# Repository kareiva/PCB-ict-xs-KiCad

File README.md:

# PCB-ict-xs-KiCad

The ICT tracker KiCad PCB imported from @micked99's Eagle version

Based on original ict_v361-xs, using the QFN/MLF version of the 328p.

Software for this board: https://github.com/kareiva/ICT-v5-ATGM336

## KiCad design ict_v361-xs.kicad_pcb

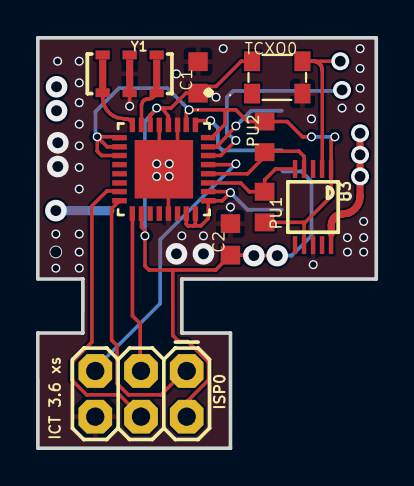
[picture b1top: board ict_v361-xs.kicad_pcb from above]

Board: 2 copper layers, 18.8 x 22.8 mm, 10 parts (1 on the bottom side), 16 nets.

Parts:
C1, C2: C0603K
ISP0: 2X3
PU1, PU2: R0603
TCXO0: 3.2X2.5_KXO-84-TCXO
U3: Si5351; MSOP10
U4: ATMEGA328P-MU; QFN50P500X500X100-33N
U$2: UBLOX_MAX
Y1: RESONATOR-SMD-4.5X2.0

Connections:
ENABLE: PU1.2, PU2.2, U3.1, U3.7, U4.2, U4.9, U4.10, U4.11, U4.32
GND: C1.2, C2.2, ISP0.6, TCXO0.2, U3.8, U4.3, U4.5, U4.21, U4.33, U$2.1_GND, U$2.10_GND, U$2.12_GND, Y1.2
GPS-OFF: U4.1, U$2.5_EXTINT0
GPS_POWER: U4.23, U4.24, U4.25, U4.26, U$2.8_VCC
MISO: ISP0.1, U4.16
MOSI: ISP0.4, U4.15
unnamed: U4.7, Y1.3
unnamed: U4.8, Y1.1
unnamed: TCXO0.3, U3.2
RESET: ISP0.5, U4.29
SCK: ISP0.3, U4.17
SCL: PU2.1, U3.4, U4.28
SDA: PU1.1, U3.5, U4.27
SERIAL_IN: U4.30, U$2.2_TXD1
SERIAL_OUT: U4.31, U$2.3_RXD1
VIN: C1.1, C2.1, ISP0.2, TCXO0.4, U4.4, U4.6, U4.18, U$2.6_V_BCKP

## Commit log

2022-05-09 Import from micked99 Eagle xs version to KiCad6
2022-05-09 Make the ISP pin path narrower
